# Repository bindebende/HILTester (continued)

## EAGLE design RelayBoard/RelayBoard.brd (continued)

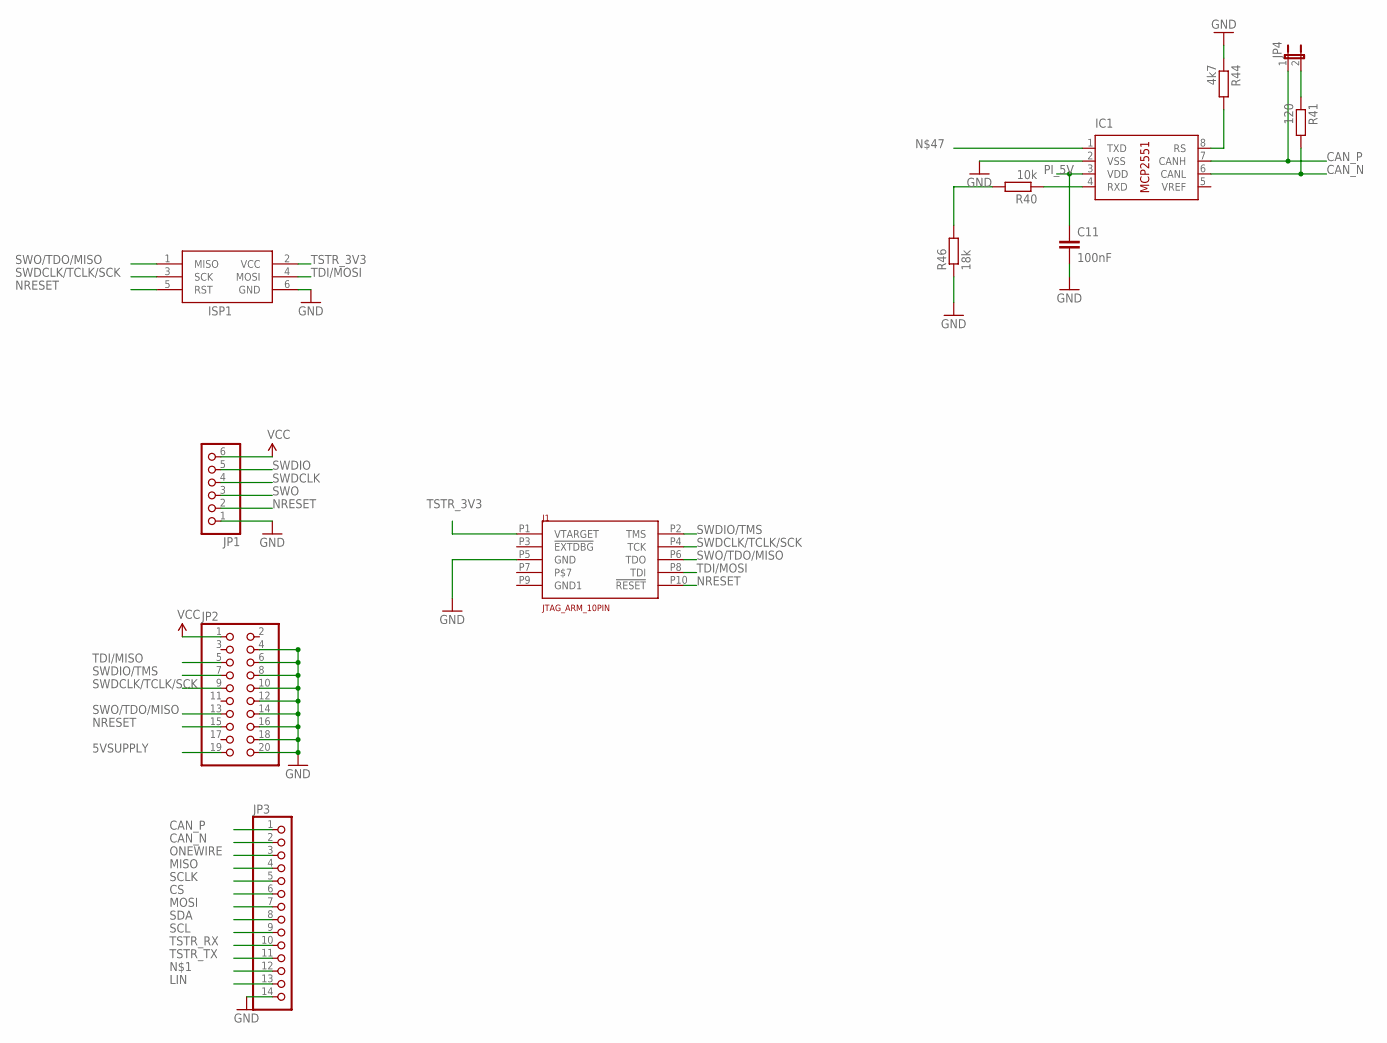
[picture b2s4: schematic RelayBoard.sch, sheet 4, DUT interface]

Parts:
C11: 100nF; C0402
IC1: MCP2551/SN RSC 402-904; SO08
ISP1: AVRISP-6; AVRISP
J1: JTAG_ARM_10PIN; CON_2X5_50MIL
JP1: PINHD-1X6B; 1X06-BIG
JP2: PINHD-2X10; 2X10
JP3: PINHD-1X14; 1X14
JP4: JUMPER-2SMD-NO; SJ_2S-NO
R40: 10k; R0402
R41: 120; R0402
R44: 4k7; R0402
R46: 18k; R0402

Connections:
5VSUPPLY: JP2.19
CAN_N: IC1.6 (CANL), JP3.2, R41.2
CAN_P: IC1.7 (CANH), JP3.1, JP4.1
CS: JP3.6
GND: C11.2, IC1.2 (VSS), ISP1.6 (GND), J1.P5 (GND), JP1.1, JP2.4, JP2.6, JP2.8, JP2.10, JP2.12, JP2.14, JP2.16, JP2.18, JP2.20, JP3.14, R44.1, R46.1; also elsewhere on the board
LIN: JP3.13
MISO: JP3.4
MOSI: JP3.7
unnamed: JP4.2, R41.1
unnamed: R40.2, R46.2
unnamed: IC1.4 (RXD), R40.1
unnamed: IC1.8 (RS), R44.2
NRESET: ISP1.5 (RST), J1.P10 (!RESET), JP1.2, JP2.15
ONEWIRE: JP3.3
PI_5V: C11.1, IC1.3 (VDD)
SCL: JP3.9
SCLK: JP3.5
SDA: JP3.8
SWDCLK: JP1.4
SWDCLK/TCLK/SCK: ISP1.3 (SCK), J1.P4 (TCK), JP2.9
SWDIO: JP1.5
SWDIO/TMS: J1.P2 (TMS), JP2.7
SWO: JP1.3
SWO/TDO/MISO: ISP1.1 (MISO), J1.P6 (TDO), JP2.13
TDI/MISO: JP2.5
TDI/MOSI: ISP1.4 (MOSI), J1.P8 (TDI)
TSTR_3V3: ISP1.2 (VCC), J1.P1 (VTARGET); also elsewhere on the board
TSTR_RX: JP3.10; also elsewhere on the board
TSTR_TX: JP3.11; also elsewhere on the board
VCC: JP1.6, JP2.1; also elsewhere on the board

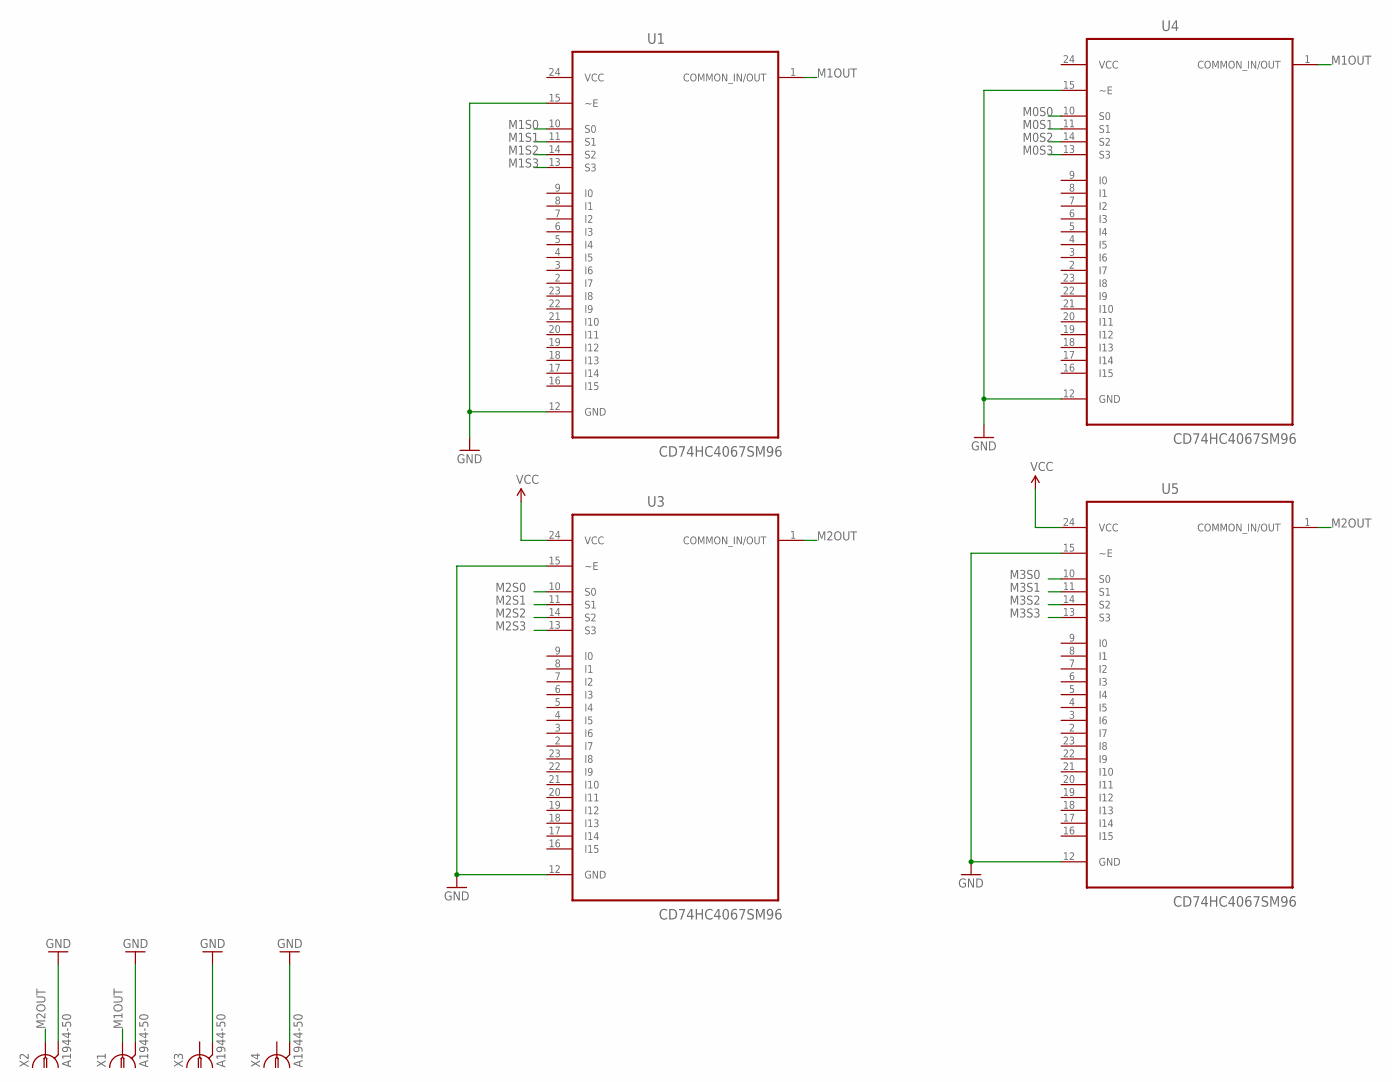
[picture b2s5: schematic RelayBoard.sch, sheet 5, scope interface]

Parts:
U1, U3, U4, U5: CD74HC4067SM96; SOP65P780X200-24N
X1, X2, X3, X4: A1944-50; A1944

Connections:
GND: U1.12 (GND), U1.15 (~E), U3.12 (GND), U3.15 (~E), U4.12 (GND), U4.15 (~E), U5.12 (GND), U5.15 (~E), X1.2, X1.3 (2), X1.4 (2), X1.5 (2), X2.2, X2.3 (2), X2.4 (2), X2.5 (2), X3.2, X3.3 (2), X3.4 (2), X3.5 (2), X4.2, X4.3 (2), X4.4 (2), X4.5 (2); also elsewhere on the board
M0S0: U4.10 (S0)
M0S1: U4.11 (S1)
M0S2: U4.14 (S2)
M0S3: U4.13 (S3)
M1OUT: U1.1 (COMMON_IN/OUT), U4.1 (COMMON_IN/OUT), X1.1
M1S0: U1.10 (S0)
M1S1: U1.11 (S1)
M1S2: U1.14 (S2)
M1S3: U1.13 (S3)
M2OUT: U3.1 (COMMON_IN/OUT), U5.1 (COMMON_IN/OUT), X2.1
M2S0: U3.10 (S0)
M2S1: U3.11 (S1)
M2S2: U3.14 (S2)
M2S3: U3.13 (S3)
M3S0: U5.10 (S0)
M3S1: U5.11 (S1)
M3S2: U5.14 (S2)
M3S3: U5.13 (S3)
VCC: U1.24 (VCC), U3.24 (VCC), U4.24 (VCC), U5.24 (VCC); also elsewhere on the board

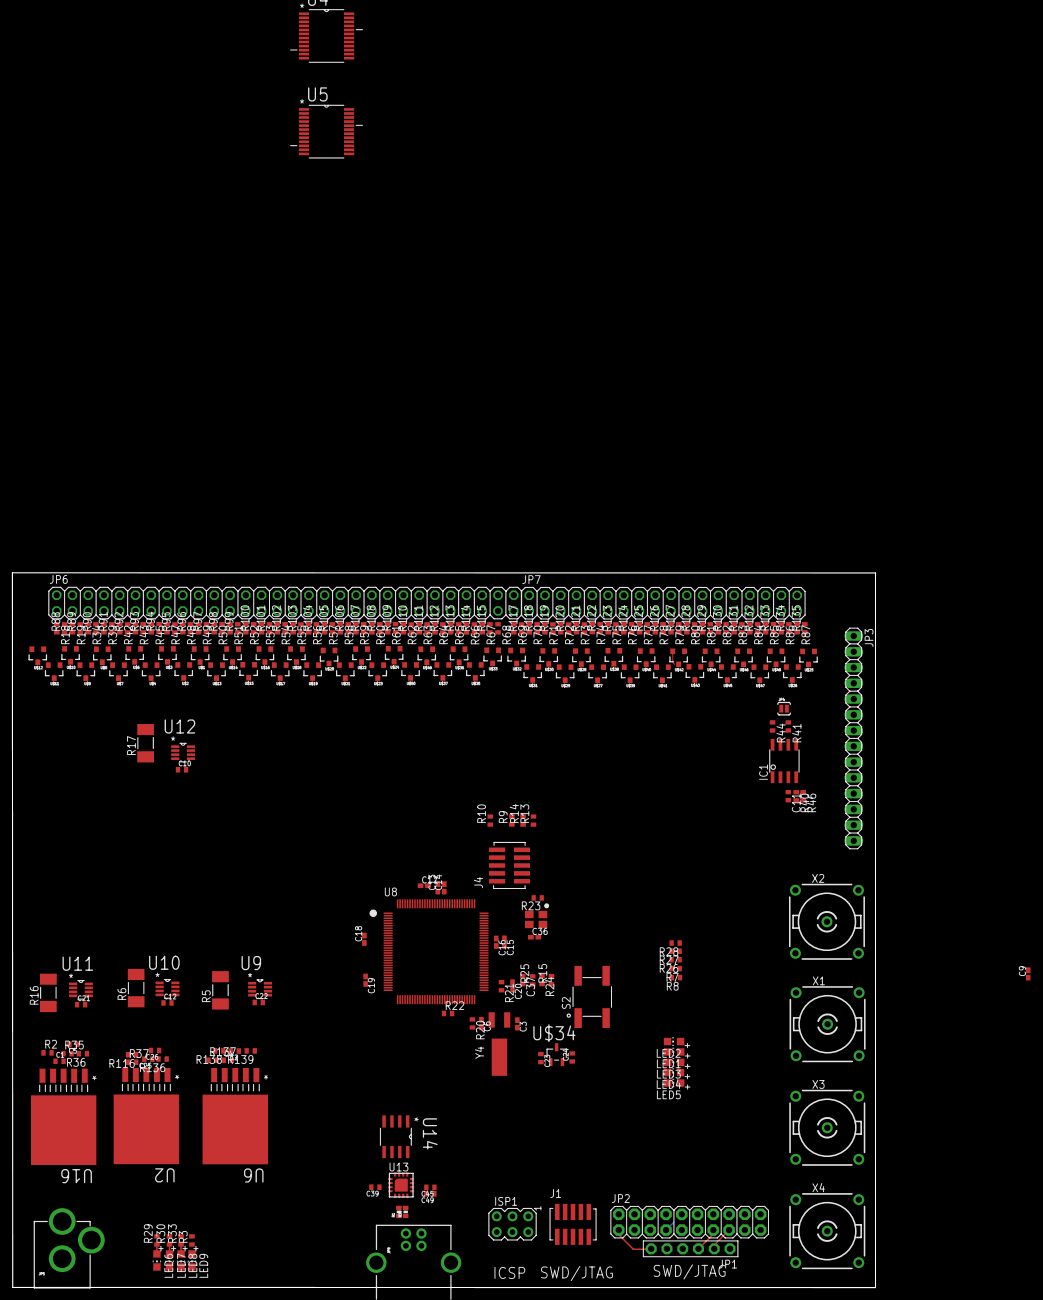
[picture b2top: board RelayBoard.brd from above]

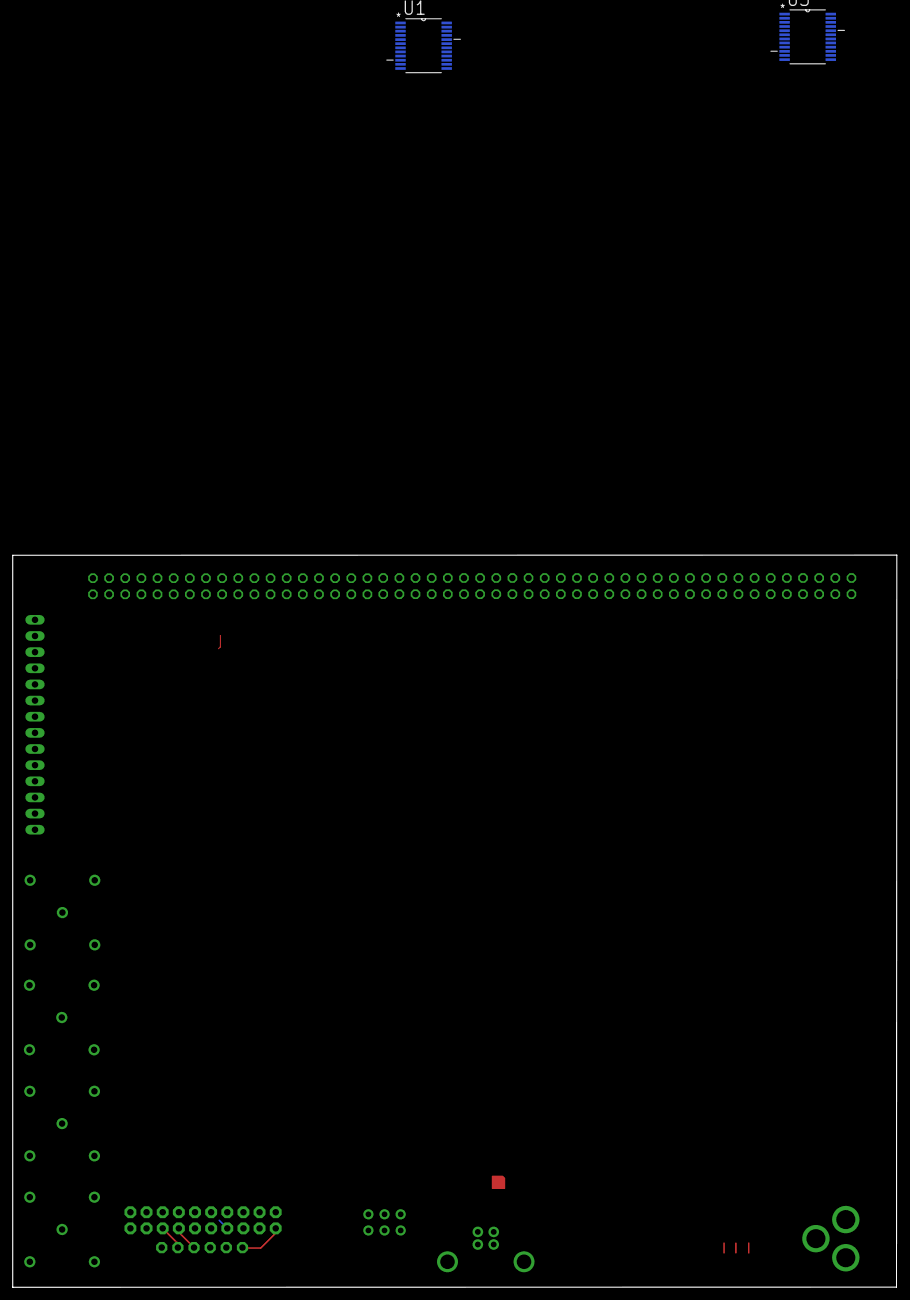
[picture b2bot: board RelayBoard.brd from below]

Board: 2 copper layers, 139.1 x 115.2 mm, 254 parts (2 on the bottom side), 256 nets.

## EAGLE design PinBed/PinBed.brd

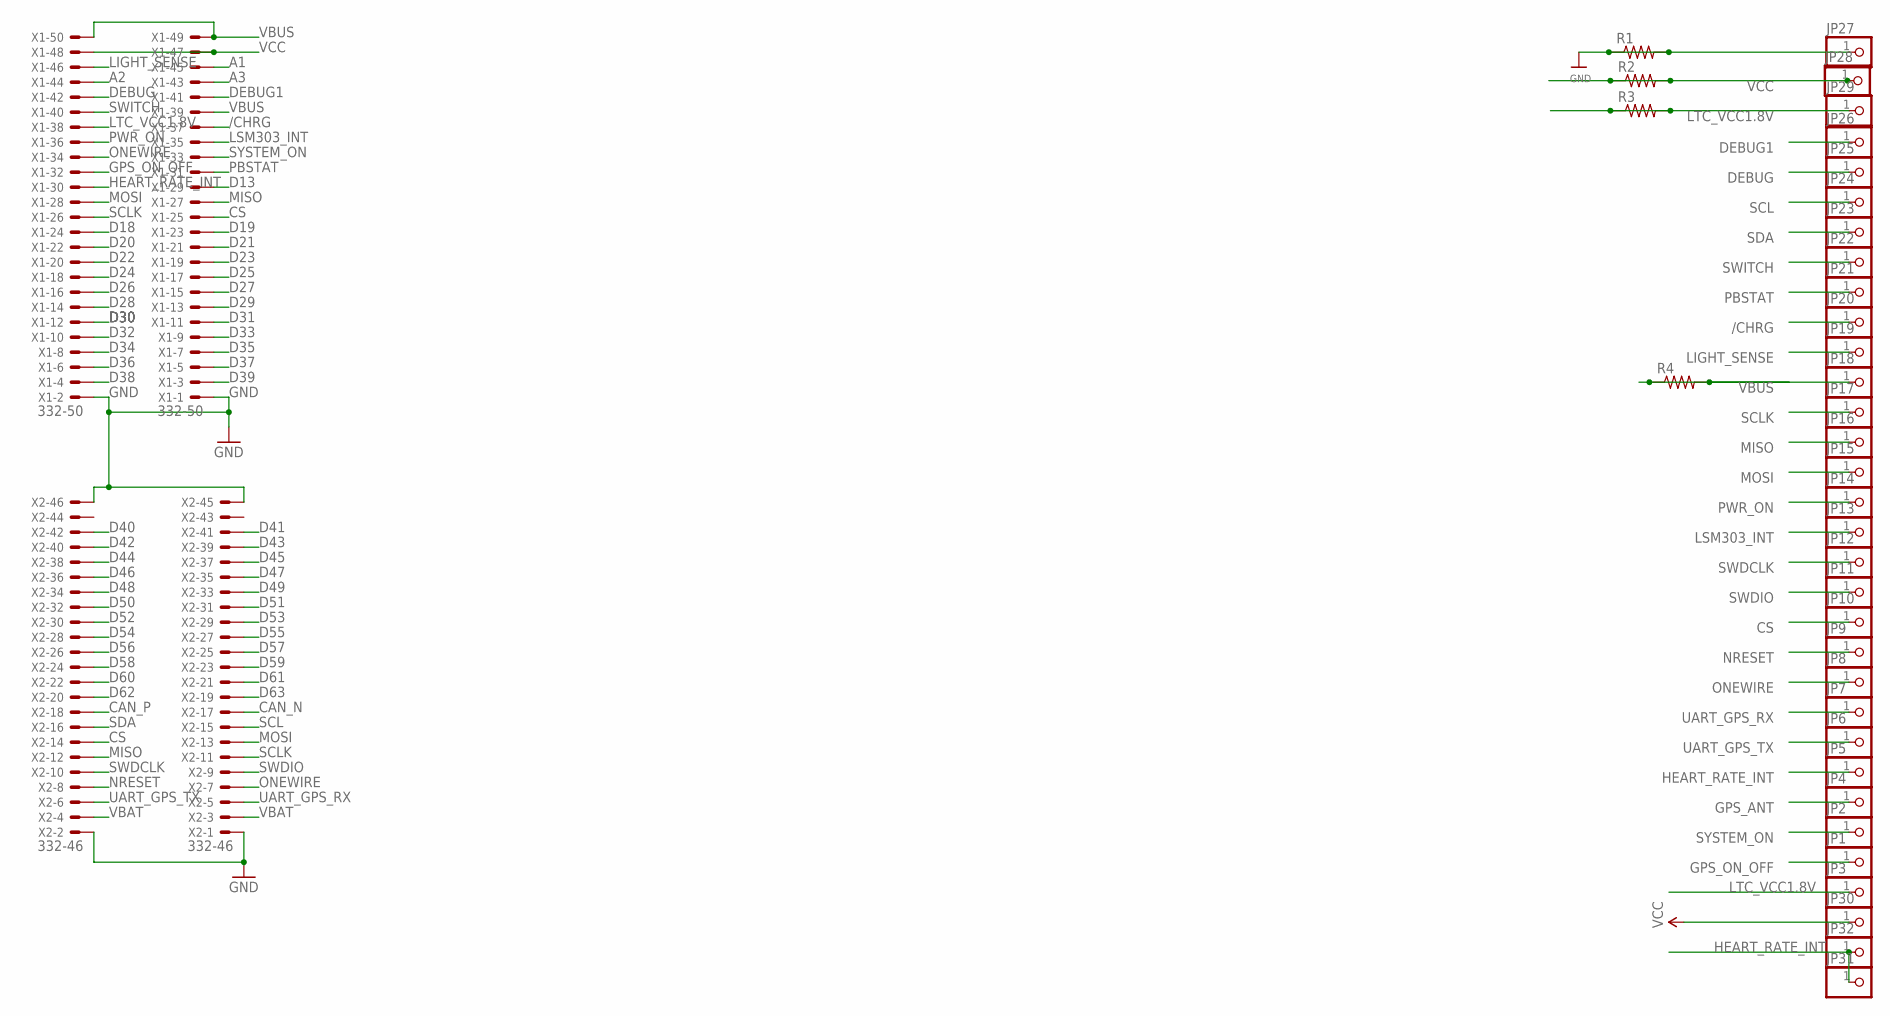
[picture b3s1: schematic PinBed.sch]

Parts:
JP1, JP2, JP3, JP4, JP5, JP6, JP7, JP8, JP9, JP10, JP11, JP12, JP13, JP14, JP15, JP16, JP17, JP18, JP19, JP20, JP21, JP22, JP23, JP24, JP25, JP26, JP27, JP28, JP29, JP30, JP31, JP32: PINHD-1X1CB; 1X01-CLEANBIG
R1, R2, R3, R4: RESISTOR0805-RES; 0805
X1: 332-50
X2: 332-46

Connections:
/CHRG: JP20.1, X1.37
A1: X1.45
A2: X1.44
A3: X1.43
CAN_N: X2.17
CAN_P: X2.18
CS: JP10.1, X1.25, X2.14
D13: X1.29
D18: X1.24
D19: X1.23
D20: X1.22
D21: X1.21
D22: X1.20
D23: X1.19
D24: X1.18
D25: X1.17
D26: X1.16
D27: X1.15
D28: X1.14
D29: X1.13
D30: X1.12
D31: X1.11
D32: X1.10
D33: X1.9
D34: X1.8
D35: X1.7
D36: X1.6
D37: X1.5
D38: X1.4
D39: X1.3
D40: X2.42
D41: X2.41
D42: X2.40
D43: X2.39
D44: X2.38
D45: X2.37
D46: X2.36
D47: X2.35
D48: X2.34
D49: X2.33
D50: X2.32
D51: X2.31
D52: X2.30
D53: X2.29
D54: X2.28
D55: X2.27
D56: X2.26
D57: X2.25
D58: X2.24
D59: X2.23
D60: X2.22
D61: X2.21
D62: X2.20
D63: X2.19
DEBUG: JP25.1, X1.42
DEBUG1: JP26.1, X1.41
GND: JP27.1, R1.1, R1.2, X1.1, X1.2, X2.1, X2.2, X2.45, X2.46
GPS_ANT: JP4.1
GPS_ON_OFF: JP1.1, X1.32
HEART_RATE_INT: JP5.1, JP31.1, JP32.1, X1.30
LIGHT_SENSE: JP19.1, X1.46
LSM303_INT: JP13.1, X1.35
LTC_VCC1.8V: JP3.1, JP29.1, R3.1, R3.2, X1.38
MISO: JP16.1, X1.27, X2.12
MOSI: JP15.1, X1.28, X2.13
NRESET: JP9.1, X2.8
ONEWIRE: JP8.1, X1.34, X2.7
PBSTAT: JP21.1, X1.31
PWR_ON: JP14.1, X1.36
SCL: JP24.1, X2.15
SCLK: JP17.1, X1.26, X2.11
SDA: JP23.1, X2.16
SWDCLK: JP12.1, X2.10
SWDIO: JP11.1, X2.9
SWITCH: JP22.1, X1.40
SYSTEM_ON: JP2.1, X1.33
UART_GPS_RX: JP7.1, X2.5
UART_GPS_TX: JP6.1, X2.6
VBAT: X2.3, X2.4
VBUS: JP18.1, R4.1, R4.2, X1.39, X1.49, X1.50
VCC: JP28.1, JP30.1, R2.1, R2.2, X1.47, X1.48

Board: 2 copper layers, 38 parts (0 on the bottom side), 28 nets, no tracks yet.

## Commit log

2017-05-20 First initial commit of the tester moved from neogeo
2017-06-04 remove: - ioexpanders add: - tm4c129 mcu - plus two multiplexer and two BNC connector - 139x115mm board size
2017-06-05 additions
    - common connector for isp, jtag, swd
    - change LDOs to the one which have Enable pin
    - UART -> USB interface and isolator to the uart side
    - dedicated MCU supply
2017-10-09 layout done
    Add: - binding posts with 19.05 mm spacing
    - top/bottom VCC/GND plane
2017-10-09 Add output pdfs
2017-10-09 fix - close cap to mcu
2017-10-11 Fix issues
2017-10-11 File system change
    names: relayboard -> HIL
    rearange files to folders
2017-10-11 Add switch bypass resistor
2017-10-11 Extend plane
    Extend TSTR_3V3’s plane
2017-10-13 smal fixes
    better 3v3 plane coverage
    add labels
    fix tracks which are not straight or 45 degree
2017-10-13 Change: - MCU to a proper package Add: - labels - i2c header - UART header
2017-10-14 change the position of the holes fix component libaries
2017-10-14 Add RACK.brd to evaluate the dimensions of the rack
2017-10-15 Add panels to RACK.brd
2017-10-16 Generate pdfs, and gerbers Libraries “>NAME” parameter change
2017-10-16 Generate BOM
2017-10-18 Rename folder PinBed to ExtensionBoards
2017-10-19 Fix: - Vcc pin present in the schematic Add: - digital tersistor to the schematic - measurements of the holes/drills
2017-10-23 Remove: 1 chanel DAC Add: 8 CH DAC Update: libraries
2017-10-24 Add: - dac headers - labels to all the headers
2017-10-25 Add DAC layout
2018-02-04 start the A3.0
